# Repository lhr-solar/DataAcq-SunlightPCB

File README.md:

# Telemetry Leader Board
Authors: Chase Block and Sijin Woo

Firmware: https://github.com/lhr-solar/Sunlight

This hardware includes a GPS, IMU, SD Card Reader, CAN interface, and Ethernet interface.
The software on this board is responsible for data collection on the solar vehicle.

## BOM
[**Interactive BOM (Must download and open in browser)**](ibom.html)

[**Mouser Cart (GPS module purchased directly from Adafruit)**](https://www.mouser.com/ProjectManager/ProjectDetail.aspx?AccessID=f18cbb5175)

## Connectors
| # | Name | Type | Pin 1 | 2 | 3 | 4 | 5 | 6 | Notes |
| - | - | - | - | - | - | - | - | - | - |
| J1  | CAN Logic Analyzer | 1x3xP2.54mm Female | GND | TX | RX | | | | |
| J2  | IMU Logic Analyzer | 1x5xP2.54mm Female | GND | SCL | SDA | INT | RESET | | I2C |
| J3  | GPS Logic Analyzer | 1x5xP2.54mm Female | GND | TX | RX | FIX | 1PPS | | USART |
| J4  | Serial Wire Debug | 1x4xP2.54mm Female | +3.3V | SWCLK | SWDIO | GND | | | Flashing |
| J5  | SD Logic Analyzer | 1x6xP2.54mm Female | GND | CS | MOSI | CLK | MISO | DET | SPI |
| J6  | N/A | | | | | | | | Vestigial annotation |
| J7  | 12V Power | 1x2xP3.00mm Molex Micro-Fit Female | +12V | GNDPWR | | | | | Primary power board |
| J8  | Ethernet | RJ45 | | | | | | | Refer to [Sunlight](https://github.com/lhr-solar/Sunlight) repo for radio connections |
| J9  | Storage | microSD Card | | | | | | | Local logging |
| J10 | GPS Antenna | SMA Male | | | | | | | Extends range |
| J11 | Serial Debugger | USB Micro B Male | | | | | | | At 115,200 bauds, [PuTTY](https://www.putty.org/) |
| J12 | CAN In | 1x4xP3.00mm Molex Micro-Fit Female | +5V | GND | CAN_H | CAN_L | | | Interchangable with J13 |
| J13 | CAN Out | 1x4xP3.00mm Molex Micro-Fit Female | +5V | GND | CAN_H | CAN_L | | | Refer to JP1 below if end of bus |

## Operational Components
| Component | Name | Notes |
| - | - | - |
| JP1 | CAN Endpoint | Close if end of bus |
| SW1  | Board Reset | Click to reset STM |
| SW2  | RTC Battery Check | Hold for status LED |
| SW3  | GPS Battery Check | Hold for status LED |
| BT1  | RTC Battery | CR1220 |
| BT2  | GPS Battery | CR1220 |

## PCB
[**PDF without traces**](Telemetry-PrimaryPCB.pdf)

## Schematic
[**PDF with all sheets**](Telemetry-PrimarySCH.pdf)

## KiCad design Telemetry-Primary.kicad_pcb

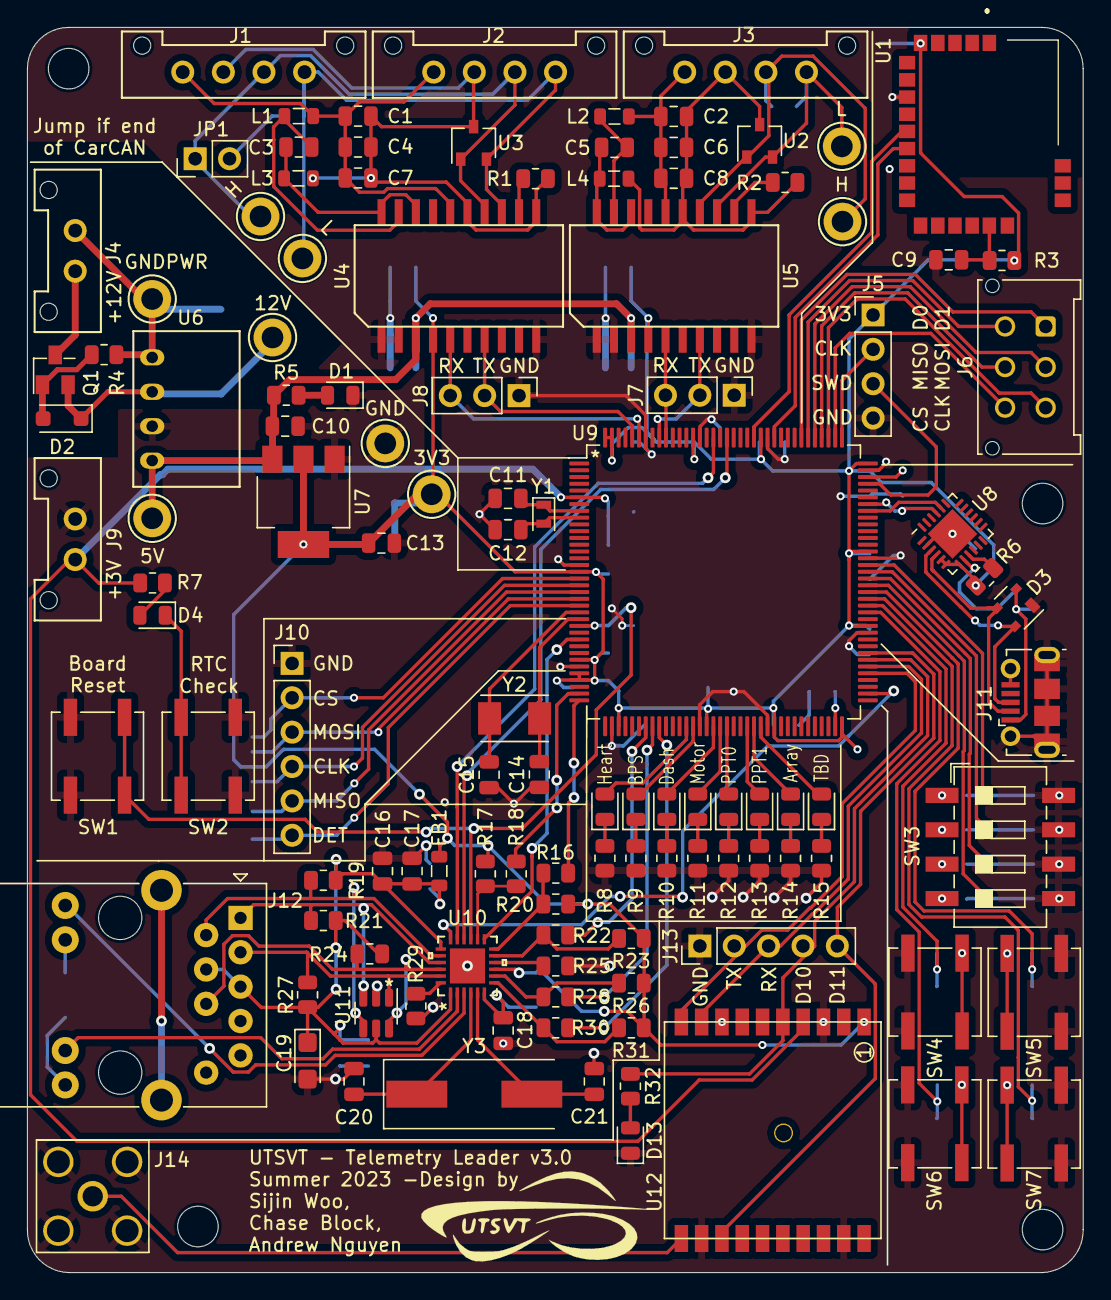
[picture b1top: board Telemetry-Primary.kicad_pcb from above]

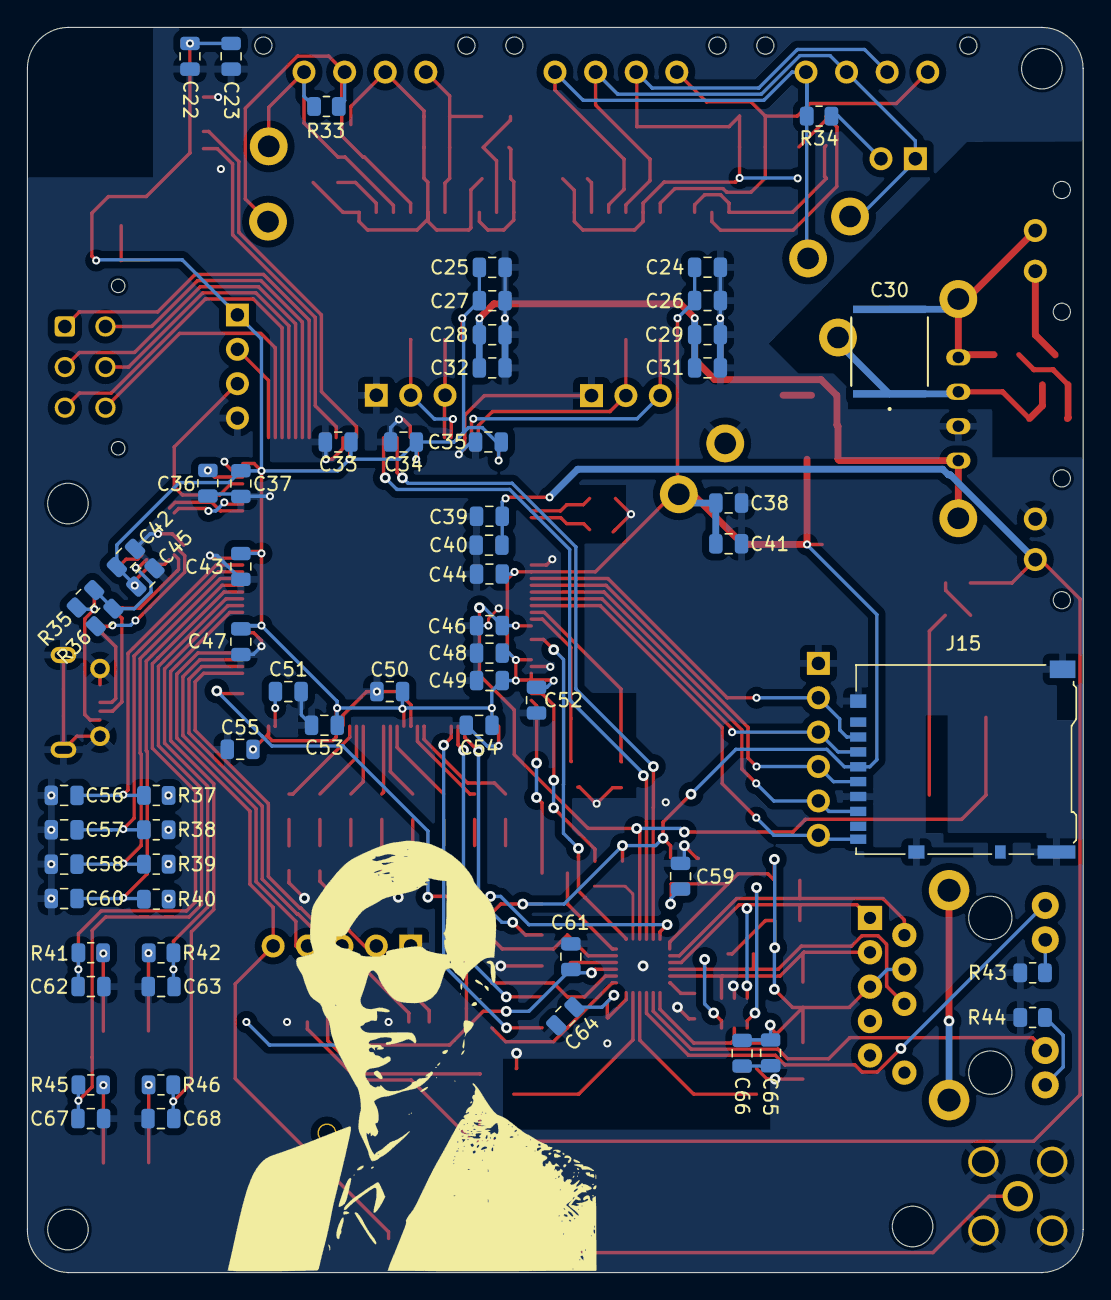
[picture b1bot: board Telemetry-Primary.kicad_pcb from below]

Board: 2 copper layers, 78.0 x 92.0 mm, 186 parts (63 on the bottom side), 126 nets.

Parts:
C1, C2, C10, C13, C22, C31, C32: 10u; C_0805_2012Metric
C3, C5: 0.22u; C_0805_2012Metric
C4, C6, C16, C17, C23, C26, C27, C28, C29, C33, C34, C35, C36, C37, C40, C43, C44, C45, C46, C47, C48, C49, C50, C51, C53, C55, C59, C61, C65, C66: 0.1u; C_0805_2012Metric
C7, C8, C24, C25: 0.01u; C_0805_2012Metric
C9: 10n; C_0805_2012Metric
C11, C12: 9p; C_0805_2012Metric
C14, C15: 18p; C_0805_2012Metric
C18, C38, C52: 1u; C_0805_2012Metric
C19: 10u; CP_EIA-3216-18_Kemet-A
C20, C21: 30p; C_0805_2012Metric
C30: 10u; C_2220_5750Metric
C39, C42, C54: 4.7u; C_0805_2012Metric
C41, C56, C57, C58, C60, C62, C63, C67, C68: .1u; C_0805_2012Metric
C64: 470p; C_0805_2012Metric
D1: PowerOn; LED_0805_2012Metric
D2: D_Zener; D_SOD-123F
D3: SP0503BAHTG; SOT-143
D4: RTCC_BattCheck; LED_0805_2012Metric
D5: Heartbeat; LED_0805_2012Metric
D6: BPS; LED_0805_2012Metric
D7: Dashboard; LED_0805_2012Metric
D8: Motor; LED_0805_2012Metric
D9: MPPT0; LED_0805_2012Metric
D10: MPPT1; LED_0805_2012Metric
D11, D12: RTDArray; LED_0805_2012Metric
D13: GPS_FIX; LED_0805_2012Metric
FB1: 600; L_0805_2012Metric
H1, H2, H3, H4: M.3; MountingHole_3mm
J1: CAN_In; Molex_MicroFit3.0_1x4xP3.00mm_PolarizingPeg_Vertical
J2, J3: CAN_Out; Molex_MicroFit3.0_1x4xP3.00mm_PolarizingPeg_Vertical
J4: PowerConn; Molex_MicroFit3.0_1x2xP3.00mm_PolarizingPeg_Vertical
J5: SWD; PinHeader_1x04_P2.54mm_Vertical
J6: Breakouts; Molex_Micro-Fit_3.0_43045-0612_2x03_P3.00mm_Vertical
J7, J8: CAN_LogicAnalyzer; PinHeader_1x03_P2.54mm_Vertical
J9: RTC_BATT; Molex_MicroFit3.0_1x2xP3.00mm_PolarizingPeg_Vertical
J10: SDCard_LogicAnalyzer; PinHeader_1x06_P2.54mm_Vertical
J11: USB_B_Micro; USB_Micro-B_Molex-105017-0001
J12: RJ45_Abracon_ARJP11A-MASA-B-A-EMU2; RJ45_Abracon_ARJP11A-MA_Horizontal
J13: GPS_LogicAnalyzer; PinHeader_1x05_P2.54mm_Vertical
J14: SMAConn; SMA_Amphenol_132203-12_Horizontal
J15: Micro_SD_Card_Det; microSD_HC_Hirose_DM3AT-SF-PEJM5
JP1: Termination RES; PinHeader_1x02_P2.54mm_Vertical
L1, L2, L3, L4: 2k; L_0805_2012Metric
LOGO1: UTSVT Logo; UTSVT_Logo_Symbol
LOGO2: Dr. Hallock; Hallock_Image
Q1: Q_PMOS_GSD; SuperSOT-3
R1, R2: 0; R_0805_2012Metric
R3: 47k; R_0805_2012Metric
R4: 10; R_0805_2012Metric
R5, R20: 1.5k; R_0805_2012Metric
R6, R37, R38, R39, R40, R41, R42, R45, R46: 1k; R_0805_2012Metric
R7: 550; R_0805_2012Metric
R8: 680; R_0805_2012Metric
R9, R10, R11, R12, R13, R14, R15, R32: 750; R_0805_2012Metric
R16, R18, R22, R28, R30: 33; R_0805_2012Metric
R17, R23, R25, R26, R31: 10k; R_0805_2012Metric
R19, R21, R24, R27: 50; R_0805_2012Metric
R29: 12.1k; R_0805_2012Metric
R33, R34, R43, R44: 120; R_0805_2012Metric
R35: 22.1k; R_0805_2012Metric
R36: 47.5k; R_0805_2012Metric
SW1: Reset; SW_SPST_B3SL-1002P
SW2: RTCC_BattCheck; SW_SPST_B3SL-1002P
SW3: SW_DIP_x04; SW_DIP_SPSTx04_Slide_6.7x11.72mm_W8.61mm_P2.54mm_LowProfile
SW4, SW5, SW6, SW7: SW_Push; SW_SPST_B3SL-1002P
TP1, TP4: CAN_L; TestPoint_Keystone_5005-5009_Compact
TP2, TP3: CAN_H; TestPoint_Keystone_5005-5009_Compact
TP5: GNDPWR_TP; TestPoint_Keystone_5005-5009_Compact
TP6: +12V_TP; TestPoint_Keystone_5005-5009_Compact
TP7: GND_TP; TestPoint_Keystone_5005-5009_Compact
TP8: +3.3V_TP; TestPoint_Keystone_5005-5009_Compact
TP9: +5V_TP; TestPoint_Keystone_5005-5009_Compact
U1: BLUENRG-M2SA; BLUENRGM2SA
U2, U3: CDSOT23-T24CAN; SOT-23W
U4, U5: ADM3055E; SOIC-20W_7.5x15.4mm_Pitch1.27mm
U6: RI3-1205S; RI3_DC_Converter
U7: LD1117-3.3_SOT223; SOT-223-3_TabPin2
U8: CP2102N-A02-GQFN24; QFN-24-1EP_4x4mm_P0.5mm_EP2.6x2.6mm
U9: STM32F429ZITx; LQFP-144_20x20mm_P0.5mm
U10: LAN8742A-CZ-TR; LAN8742AI-CZ-TR
U11: USBLC6-4SC6; SOT-23-6
U12: MTK3339; FGPMMOPA6H
Y1: 32.768k; Crystal_SMD_2012-2Pin_2.0x1.2mm
Y2: 8M; Crystal_SMD_TXC_7A-2Pin_5x3.2mm
Y3: 25M; Crystal_SMD_HC49-SD

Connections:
+3.3V: C13.1, C22.1, C23.1, C24.1, C25.1, C26.1, C27.1, C33.1, C34.1, C35.1, C37.1, C38.1, C41.1, C42.1, C43.1, C44.1, C45.1, C47.1, C48.1, C49.1, C50.1, C52.1, C53.1, C54.1, C55.1, C61.2, FB1.1, J5.1, J15.4 (VDD), R3.1, R6.1, R17.2, R20.2, R23.1, R26.1, R31.1, TP8.1, U1.5 (VIN), U4.4 (V_IO), U5.4 (V_IO), U7.2 (VO), U8.5 (VIO), U8.6 (VDD), U8.7 (VREGIN), U9.17 (VDD), U9.30 (VDD), U9.32 (VREF+), U9.33 (VDDA), U9.39 (VDD), U9.52 (VDD), U9.62 (VDD), U9.72 (VDD), U9.84 (VDD), U9.95 (VDD), U9.108 (VDD), U9.121 (VDD), U9.131 (VDD), U9.143 (PDR_ON), U9.144 (VDD), U10.9 (VDDIO), U12.1 (VCC)
+5V: C10.1, C28.1, C29.1, C31.1, C32.1, R5.1, TP9.1, U4.3 (V_In), U5.3 (V_In), U6.4 (+Vout), U7.3 (VI)
+12V: C30.1, D2.1 (K), Q1.2 (S), TP6.1, U6.2 (+Vin)
+BATT: C39.1, C40.1, J9.1, R7.1, U9.6 (VBAT), U12.4 (VBACKUP)
/CAN1_RX: J8.3, U4.5 (RX), U9.139 (PB8)
/CAN1_TX: J8.2, U4.7 (TX), U9.140 (PB9)
/CAN2_RX: J7.3, U5.5 (RX), U9.135 (PB5)
/CAN2_TX: J7.2, U5.7 (TX), U9.136 (PB6)
/CarCAN/CAN_H: J1.3 (CAN_H), J2.3 (CAN_H), JP1.1 (A), TP2.1, U3.1 (CAN_H), U4.14 (CAN_H)
/CarCAN/CAN_L: J1.4 (CAN_L), J2.4 (CAN_L), R34.2, TP4.1, U3.2 (CAN_L), U4.13 (CAN_L)
/CarCAN/RSlope: R1.1, U4.12 (RS)
/Ethernet/LED1: J12.11 (LLED+), U10.3 (LED1/nINT/nPME/REGOFF)
/Ethernet/LED2: J12.13 (RLED+), U10.2 (LED2/nINT/nPME/nINTSEL)
/Ethernet/RX+: J12.3 (RD+), R27.2, U10.23 (RXP), U11.1 (I/O1)
/Ethernet/RX-: J12.6 (RD-), R24.2, U10.22 (RXN), U11.6 (I/O4)
/Ethernet/TX+: J12.1 (TD+), R21.2, U10.21 (TXP), U11.3 (I/O2)
/Ethernet/TX-: J12.2 (TD-), R19.2, U10.20 (TXN), U11.4 (I/O3)
/NRST: C46.1, SW1.1, U9.25 (NRST), U10.15 (nRST)
/PD0: J6.4, U9.114 (PD0)
/PD1: J6.1, U9.115 (PD1)
/PD10: J13.4, R32.1, U9.79 (PD10), U12.5 (3D-FIX)
/PD11: J13.5, U9.80 (PD11), U12.13 (1PPS)
/PD15: C68.1, R46.1, U9.86 (PD15)
/PE7: D10.2 (A), U9.58 (PE7)
/PE8: D11.2 (A), U9.59 (PE8)
/PE9: D12.2 (A), U9.60 (PE9)
/PF11: D5.2 (A), U9.49 (PF11)
/PF12: D6.2 (A), U9.50 (PF12)
/PF13: D7.2 (A), U9.53 (PF13)
/PF14: D8.2 (A), U9.54 (PF14)
/PF15: D9.2 (A), U9.55 (PF15)
/PG2: C63.1, R42.1, U9.87 (PG2)
/PG3: C67.1, R45.1, U9.88 (PG3)
/PG4: C62.1, R41.1, U9.89 (PG4)
/PG5: C60.1, R40.1, U9.90 (PG5)
/PG6: C58.1, R39.1, U9.91 (PG6)
/PG7: C57.1, R38.1, U9.92 (PG7)
/PG8: C56.1, R37.1, U9.93 (PG8)
/RMII_CRS_DV: R22.2, U9.43 (PA7)
/RMII_MDC: U9.27 (PC1), U10.13 (MDC)
/RMII_MDIO: R16.2, U9.36 (PA2)
/RMII_REF_CLK: R18.2, U9.35 (PA1)
/RMII_RXD0: R28.2, U9.44 (PC4)
/RMII_RXD1: R30.2, U9.45 (PC5)
/RMII_TXD0: U9.128 (PG13), U10.17 (TXD0)
/RMII_TXD1: U9.74 (PB13), U10.18 (TXD1)
/RMII_TX_EN: U9.126 (PG11), U10.16 (TXEN)
/SD_DET: J10.6, J15.9 (DET_B), U9.22 (PF10)
/SPI3_CLK: J6.3, U9.111 (PC10)
/SPI3_CS: J6.6, U9.110 (PA15)
/SPI3_MISO: J6.5, U9.112 (PC11)
/SPI3_MOSI: J6.2, U9.113 (PC12)
/SPI5_CLK: J10.4, J15.5 (CLK), U9.19 (PF7)
/SPI5_CS: J10.2, J15.2 (DAT3/CD), U9.18 (PF6)
/SPI5_MISO: J10.5, J15.7 (DAT0), U9.20 (PF8)
/SPI5_MOSI: J10.3, J15.3 (CMD), U9.21 (PF9)
/SWCLK: J5.2, U9.109 (PA14)
/SWDIO: J5.3, U9.105 (PA13)
/TelemetryCAN/CAN_H: J3.3 (CAN_H), R33.1, TP3.1, U2.1 (CAN_H), U5.14 (CAN_H)
/TelemetryCAN/CAN_L: J3.4 (CAN_L), R33.2, TP1.1, U2.2 (CAN_L), U5.13 (CAN_L)
/TelemetryCAN/RSlope: R2.1, U5.12 (RS)
/USART1_RX: U8.21 (TXD), U9.102 (PA10)
/USART1_TX: U8.20 (RXD), U9.101 (PA9)
/USART2_RX: U1.10 (DIO8), U9.122 (PD6)
/USART2_TX: U1.11 (DIO11), U9.119 (PD5)
/USART3_RX: J13.3, U9.78 (PD9), U12.9 (TX)
/USART3_TX: J13.2, U9.77 (PD8), U12.10 (RX)
GND: C9.2, C10.2, C11.1, C12.1, C13.2, C14.1, C15.2, C16.1, C17.1, C18.1, C19.2, C20.2, C21.2, C22.2, C23.2, C24.2, C25.2, C26.2, C27.2, C28.2, C29.2, C31.2, C32.2, C33.2, C34.2, C35.2, C36.2, C37.2, C38.2, C39.2, C40.2, C41.2, C42.2, C43.2, C44.2, C45.2, C46.2, C47.2, C48.2, C49.2, C50.2, C51.2, C52.2, C53.2, C54.2, C55.2, C56.2, C57.2, C58.2, C59.1, C60.2, C61.1, C62.2, C63.2, C64.1, C65.1, C66.1, C67.2, C68.2, D1.1 (K), D3.1 (A), D13.1 (K), J5.4, J7.1, J8.1, J9.2, J10.1, J11.5 (GND), J11.6 (Shield), J13.1, J14.2 (Ext), J15.6 (VSS), J15.11 (SHIELD), R8.2, R9.2, R10.2, R11.2, R12.2, R13.2, R14.2, R15.2, R25.2, R29.1, R36.2, R43.2, R44.2, SW1.2, SW2.2, SW3.5, SW3.6, SW3.7, SW3.8, SW4.1, SW5.1, SW6.1, SW7.1, TP7.1, U1.8 (GND_1), U4.1 (GND_In), U4.2 (GND_In), U4.10 (GND_In), U5.1 (GND_In), U5.2 (GND_In), U5.10 (GND_In), U6.3 (-Vout), U7.1 (GND), U8.2 (GND), U8.25 (GND), U9.16 (VSS), U9.31 (VSSA), U9.38 (VSS), U9.51 (VSS), U9.61 (VSS), U9.83 (VSS), U9.94 (VSS), U9.107 (VSS), U9.120 (VSS), U9.130 (VSS), U9.138 (BOOT0), U10.25 (GND_EP), U11.2 (GND), U12.3 (GND), U12.8 (GND), U12.12 (GND), U12.19 (GND)
GNDPWR: C30.2, J4.2, R4.2, TP5.1, U6.1 (-Vin)
unnamed: C3.2, L3.2, U4.18 (GND_ISO_Out), U4.20 (GND_ISO_Out)
unnamed: C5.2, L4.2, U5.18 (GND_ISO_Out), U5.20 (GND_ISO_Out)
unnamed: D1.2 (A), R5.2
unnamed: D2.2 (A), Q1.1 (G), R4.1
unnamed: D4.2 (A), R7.2
unnamed: D4.1 (K), SW2.1
unnamed: D5.1 (K), R8.1
unnamed: D6.1 (K), R9.1
unnamed: D7.1 (K), R10.1
unnamed: D8.1 (K), R11.1
unnamed: D9.1 (K), R12.1
unnamed: D10.1 (K), R13.1
unnamed: D11.1 (K), R14.1
unnamed: D12.1 (K), R15.1
unnamed: D13.2 (A), R32.2
unnamed: C1.1, C4.1, C7.1, J1.1 (5V), J2.1 (5V), L1.1, U4.16 (V_ISO_In)
unnamed: C1.2, C4.2, C7.2, J1.2 (GND), J2.2 (GND), L3.1, R1.2, U3.3 (GND), U4.11 (GND_ISO_In), U4.15 (GND_ISO_In)
unnamed: C2.1, C6.1, C8.1, J3.1 (5V), L2.1, U5.16 (V_ISO_In)
unnamed: C2.2, C6.2, C8.2, J3.2 (GND), L4.1, R2.2, U2.3 (GND), U5.11 (GND_ISO_In), U5.15 (GND_ISO_In)
unnamed: J4.1, Q1.3 (D)
unnamed: D3.4 (K), J11.3 (D+), U8.3 (D+)
unnamed: D3.3 (K), J11.2 (D-), U8.4 (D-)
unnamed: D3.2 (K), J11.1 (VBUS), R35.2
unnamed: J12.12 (LLED-), R43.1
unnamed: J12.14 (RLED-), R44.1
unnamed: J14.1 (In), U12.11 (EX_ANT)
unnamed: JP1.2 (B), R34.1
unnamed: R46.2, SW6.2
unnamed: R42.2, SW4.2
unnamed: R45.2, SW7.2
unnamed: R41.2, SW5.2
unnamed: R40.2, SW3.4
unnamed: R39.2, SW3.3
unnamed: R38.2, SW3.2
unnamed: R37.2, SW3.1
unnamed: C9.1, R3.2, U1.19 (RESETN)
unnamed: C3.1, L1.2, U4.19 (V_ISO_Out)
unnamed: C5.1, L2.2, U5.19 (V_ISO_Out)
unnamed: R35.1, R36.1, U8.8 (VBUS)
unnamed: R6.2, U8.9 (~RST)
unnamed: C11.2, U9.8 (PC14), Y1.1
unnamed: C12.2, U9.9 (PC15), Y1.2
unnamed: C15.1, U9.23 (PH0), Y2.1
unnamed: C14.2, U9.24 (PH1), Y2.2
unnamed: C51.1, U9.71 (VCAP_1)
unnamed: C36.1, U9.106 (VCAP_2)
unnamed: R22.1, R23.2, U10.11 (CRS_DV/MODE2)
unnamed: R16.1, R20.1, U10.12 (MDIO)
unnamed: R29.2, U10.24 (RBIAS)
unnamed: R26.2, R28.1, U10.8 (RXD0/MODE0)
unnamed: R30.1, R31.2, U10.7 (RXD1/MODE1)
unnamed: R25.1, U10.10 (RXER/PHYAD0)
unnamed: C16.2, C17.2, C19.1, C59.2, C65.2, C66.2, FB1.2, J12.4 (CT), J12.5 (CT), R19.1, R21.1, R24.1, R27.1, U10.1 (VDD2A), U10.19 (VDD1A), U11.5 (VBUS)
unnamed: C18.2, C64.2, U10.6 (VDDCR)
unnamed: C21.1, U10.5 (XTAL1/CLKIN), Y3.2
unnamed: C20.1, U10.4 (XTAL2), Y3.1
unnamed: R17.1, R18.1, U10.14 (nINT/REFCLK0)

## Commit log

2020-08-02 Set up for own repo
2020-09-05 Changes name of molex Power and CAN connectors to be more meaningful
2020-09-05 Changes name of molex Power and CAN connectors to be more meaningful (#1)
2020-09-15 Updates project name and submodule
2020-09-19 Adds new telemetry board schematics. Still need to place GPS and Ethernet and some main uC essentials
2020-09-19 Updates common component library
2020-09-19 Adds ethernet schematics
2020-09-19 Adds GPS module to common library
2020-09-19 Updates common submodule to include GPS
2020-09-19 Adds connects all modules except for LEDs in schematics
2020-09-19 Adds logic analyzer points and LEDs
2020-09-19 Initial layout of the Telemtry board.
    The ethernet interface needs more work.
2020-09-26 Lay out the Telemetry board.
    This is the initial draft of the Telemetry board layout. A few
    debugging pins changed (on the SD card) for easier routing.
    There is still some uncertainty with regard to the routing of the
    Ethernet traces. According to my calculations, the differential
    impedence between the RX+/- traces and the TX+/- traces is around
    150R, which is 50% higher than one source was recommending. I am
2020-10-03 Adds QuAC
2020-10-03 Makes mounting hole text invisible and updates title
2020-10-03 Fix routing near crystal.
2020-10-03 Telemetry v2.0 (#2)
    * Updates project name and submodule
    * Adds new telemetry board schematics. Still need to place GPS and Ethernet and some main uC essentials
    * Updates common component library
    * Adds ethernet schematics
    * Adds GPS module to common library
    * Updates common submodule to include GPS
2020-10-07 Update schematic symbol details with ordering info.
2020-12-06 Remove the external RTC.
    There's no need to use an external RTC on the telemetry board. The
    microcontroller itself has an internal RTC that can be powered from
    the VBAT line and a 32.768kHz oscillator.
2021-08-28 Some changes to solve errata and list of errata in v1
2021-10-02 adds necessary resistors, keep out zones, and TVS diode
2021-10-03 Adds phy resistors and moves power conn away from recom
2021-10-03 Minor adjustments
2021-10-04 Checks filled zone
2023-05-22 kicad 7, fixed 3d models, symbols, submodules
    i now realize chase has a v2.1 branch..
2023-05-22 merged v2.1 changes
    removes external RTC, cleaned up big errors, only minor warnings remain
2023-05-22 forgot to add submodule commit
2023-05-22 cleaner, still needs full checklisting
2023-05-23 neatening things up
2023-05-26 bom, gerbers, edge cuts, footprint verification
2023-05-26 sch and pcb pdfs
2023-05-26 update readme image
2023-05-29 schematic organization
2023-05-29 big readme documentation update
2023-05-29 rename pdfs, ibom
2023-05-29 links
2023-05-29 pdf update and readme correction
2023-05-29 clarity
2023-05-30 added connector types
2023-05-30 Update README.md
    Fixed CAN Logic Analyzer connection
2023-06-12 bluetooth schematic additions
2023-06-12 began input/breakout changes
2023-06-17 new bt module + preliminary reverse protection
2023-06-17 basic inputs
2023-06-24 add power ports to power dist
2023-06-24 Revert "add power ports to power dist"
    This reverts commit 2e61877daa8ca3bb2eb3a68fbb2dd0a708ef5124.
2023-06-27 switch changes, some caps, annotations
2023-07-11 layout rearranging
2023-07-11 breakout port
2023-07-11 power protection layout
2023-07-11 led fix + notes
2023-07-18 layout changes, telemetryCAN added, IMU removed
2023-07-19 inputs routing + fixed models + clock keepouts
2023-08-06 silk screen cleanup + comments

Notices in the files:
parts and their libraries:
Copyright 2016 Accelerated Designs. All rights reserved.
